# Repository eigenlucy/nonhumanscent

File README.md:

# nonhumanscent (prerelease)

MOX Array for ML-assisted Chemical Identification

Supports Bosch BSEC + AI-Studio

Made with atopile and kicad 9.

To Do:
- Test PCB
- Finish Bosch AI Studio Integration and BLE
- Add project page with calibration and usage documentation on my website
- Add store page for ordering assembled boards from moi

Created by lucy moglia <eigenlucy@proton.me>

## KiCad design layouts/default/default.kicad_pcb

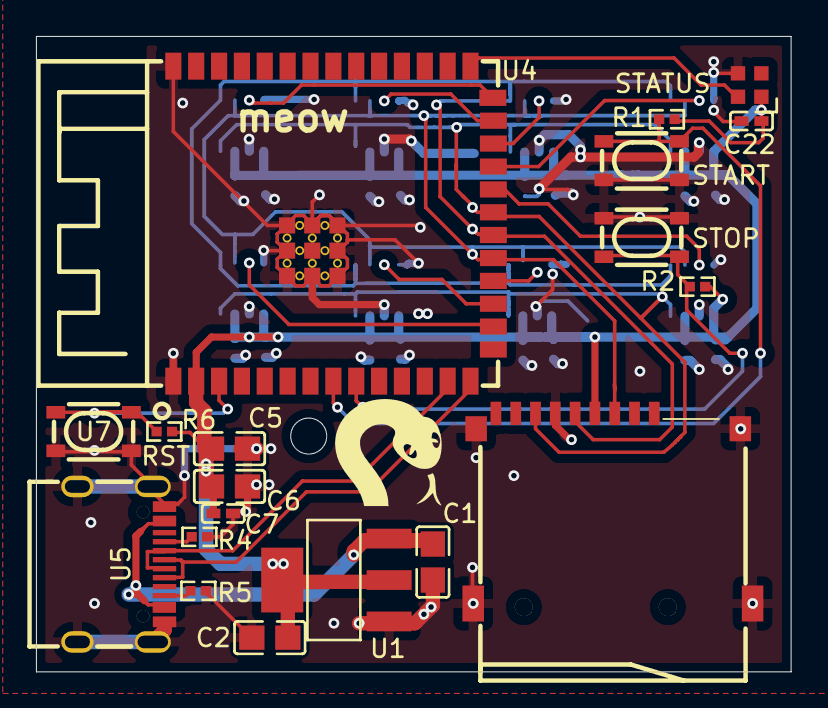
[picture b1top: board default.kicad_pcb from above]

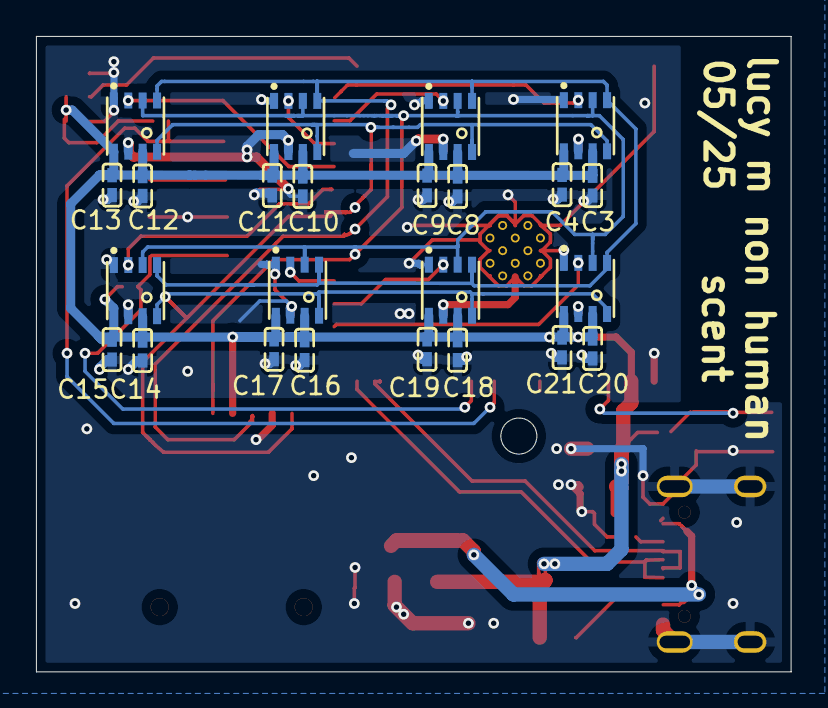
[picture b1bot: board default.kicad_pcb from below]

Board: 2 copper layers, 41.9 x 35.3 mm, 43 parts (24 on the bottom side), 22 nets.

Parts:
C1, C2: 100nF ±10% 50V X7R; C0805-3b2e55
C3, C4, C7, C8, C9, C10, C11, C12, C13, C14, C15, C16, C17, C18, C19, C20, C21, C22: 100nF ±10% 16V X7R; C0402-b3ef17
C5, C6: 10µF ±10% 25V X5R; C0805-3b2e55
R1, R2, R6: 10kΩ ±1% 62.5mW; R0402-56259e
R4, R5: 5.1kΩ ±1% 62.5mW; R0402-56259e
U1: SOT-223-3_L6.5-W3.4-P2.30-LS7.0-BR
U2, U3, U8, U9, U10, U11, U12, U13: LGA-8_L3.0-W3.0-P0.80_BME688-7465bb
U4: WIRELM-SMD_ESP32-S3-WROOM-1
U5: USB-C-SMD_KH-TYPE-C-16P
U6: TF-SMD_TF-01A
U7, U15, U16: KEY-SMD_4P-L4.2-W3.2-P2.20-LS4.6
U14: LED-SMD_4P-L2.0-W2.0-BR

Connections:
B5: R5.1, U5.B5
CC1: R4.1, U5.A5
CSB: U4.17, U12.2
CSB-1: U4.16, U13.2
CSB-2: U3.2, U4.25
CSB-3: U4.24, U8.2
CSB-4: U2.2, U4.26
CSB-5: U4.22, U10.2
CSB-6: U4.23, U9.2
DIN: U4.27, U14.4
SCK: U2.4, U3.4, U4.20, U6.5, U8.4, U9.4, U10.4, U11.4, U12.4, U13.4
SDI: U2.3, U3.3, U4.19, U6.3, U8.3, U9.3, U10.3, U11.3, U12.3, U13.3
SDO: U2.5, U3.5, U4.21, U6.7, U8.5, U9.5, U10.5, U11.5, U12.5, U13.5
gnd: C1.2, C2.2, C3.2, C4.2, C5.2, C6.2, C7.2, C8.2, C9.2, C10.2, C11.2, C12.2, C13.2, C14.2, C15.2, C16.2, C17.2, C18.2, C19.2, C20.2, C21.2, C22.2, R4.2, R5.2, U1.1, U2.1, U2.7, U3.1, U3.7, U4.1, U4.40, U4.41, U5.1, U5.2, U5.3, U5.4, U5.A1, U5.A12, U5.B1, U5.B12, U6.6, U6.10, U6.11, U6.12, U6.13, U7.3, U7.4, U8.1, U8.7, U9.1, U9.7, U10.1, U10.7, U11.1, U11.7, U12.1, U12.7, U13.1, U13.7, U14.3, U15.3, U15.4, U16.3, U16.4
hv: C2.1, C3.1, C4.1, C5.1, C6.1, C7.1, C8.1, C9.1, C10.1, C11.1, C12.1, C13.1, C14.1, C15.1, C16.1, C17.1, C18.1, C19.1, C20.1, C21.1, C22.1, R1.1, R2.1, R6.1, U1.2, U1.4, U2.6, U2.8, U3.6, U3.8, U4.2, U6.4, U8.6, U8.8, U9.6, U9.8, U10.6, U10.8, U11.6, U11.8, U12.6, U12.8, U13.6, U13.8, U14.1
hv-1: C1.1, U1.3, U5.A4, U5.A9, U5.B4, U5.B9
input: R1.2, U15.1, U15.2
input-1: R2.2, U16.1, U16.2
input-2: R6.2, U7.1, U7.2
io19: U4.13, U5.A7, U5.B7
io20: U4.14, U5.A6, U5.B6
line: U4.18, U11.2

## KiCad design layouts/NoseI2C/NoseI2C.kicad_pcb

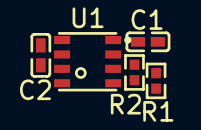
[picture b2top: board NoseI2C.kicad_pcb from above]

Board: 2 copper layers, 5 parts (0 on the bottom side), 4 nets, no tracks yet.

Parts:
C1, C2: 100nF ±10% 16V X7R; C0402-b3ef17
R1, R2: 10kΩ ±1% 62.5mW; R0402-56259e
U1: LGA-8_L3.0-W3.0-P0.80_BME688-7465bb

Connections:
SCK: R1.1, U1.4
SDI: R2.1, U1.3
VDDIO: C1.1, C2.1, R1.2, R2.2, U1.2, U1.6, U1.8
gnd: C1.2, C2.2, U1.1, U1.7

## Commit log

2025-04-26 fixed button
2025-04-26 vis of 30 min data for lemongrass, orange, lavender
2025-04-29 readme
2025-05-02 bsec 2
2025-05-03 working
2025-05-12 updated button
2025-05-19 added nose SPI interface, selectable number of sensors
2025-05-19 maintainence
2025-05-27 doneish
2025-05-28 meow
2025-05-29 fix designators and ready to order I think
2025-06-02 ordered
2025-07-14 firmware checkpoint (not working yet)
2025-07-14 fixed bme68x to nupacket data type error
2025-09-10 more
